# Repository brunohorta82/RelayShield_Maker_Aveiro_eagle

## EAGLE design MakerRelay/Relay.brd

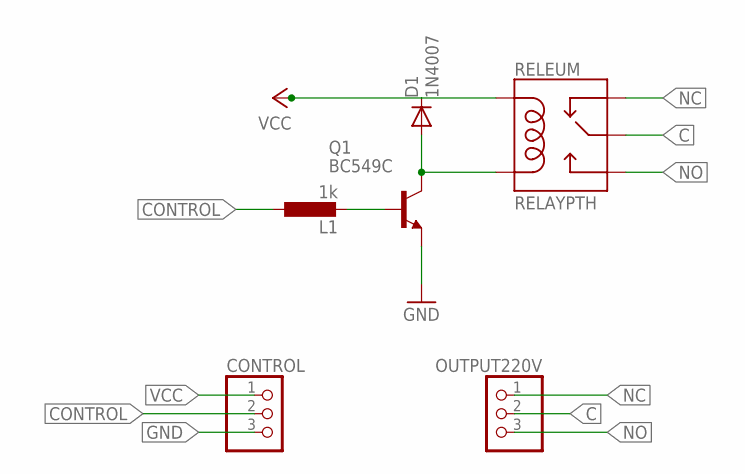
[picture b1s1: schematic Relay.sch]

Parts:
CONTROL: PINHD-1X3M; 1X03M
D1: 1N4007; DO41-10
L1: 1k; 0204/7
OUTPUT220V: PINHD-1X3M; 1X03M
Q1: BC549C; TO92-EBC
RELEUM: RELAYPTH; SRD-05VDC-SL-C

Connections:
C: OUTPUT220V.2, RELEUM.SWCOMMON
CONTROL: CONTROL.2, L1.1
GND: CONTROL.3, Q1.E
unnamed: L1.2, Q1.B
unnamed: D1.A, Q1.C, RELEUM.COIL0
NC: OUTPUT220V.1, RELEUM.SWCLOSED (SWCLOSE)
NO: OUTPUT220V.3, RELEUM.SWOPEN
VCC: CONTROL.1, D1.C, RELEUM.COIL1

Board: 2 copper layers, 6 parts (0 on the bottom side), 8 nets, no tracks yet.

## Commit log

2017-12-16 no message
